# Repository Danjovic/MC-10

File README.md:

# MC-10
Tandy MC-10 computer related stuff

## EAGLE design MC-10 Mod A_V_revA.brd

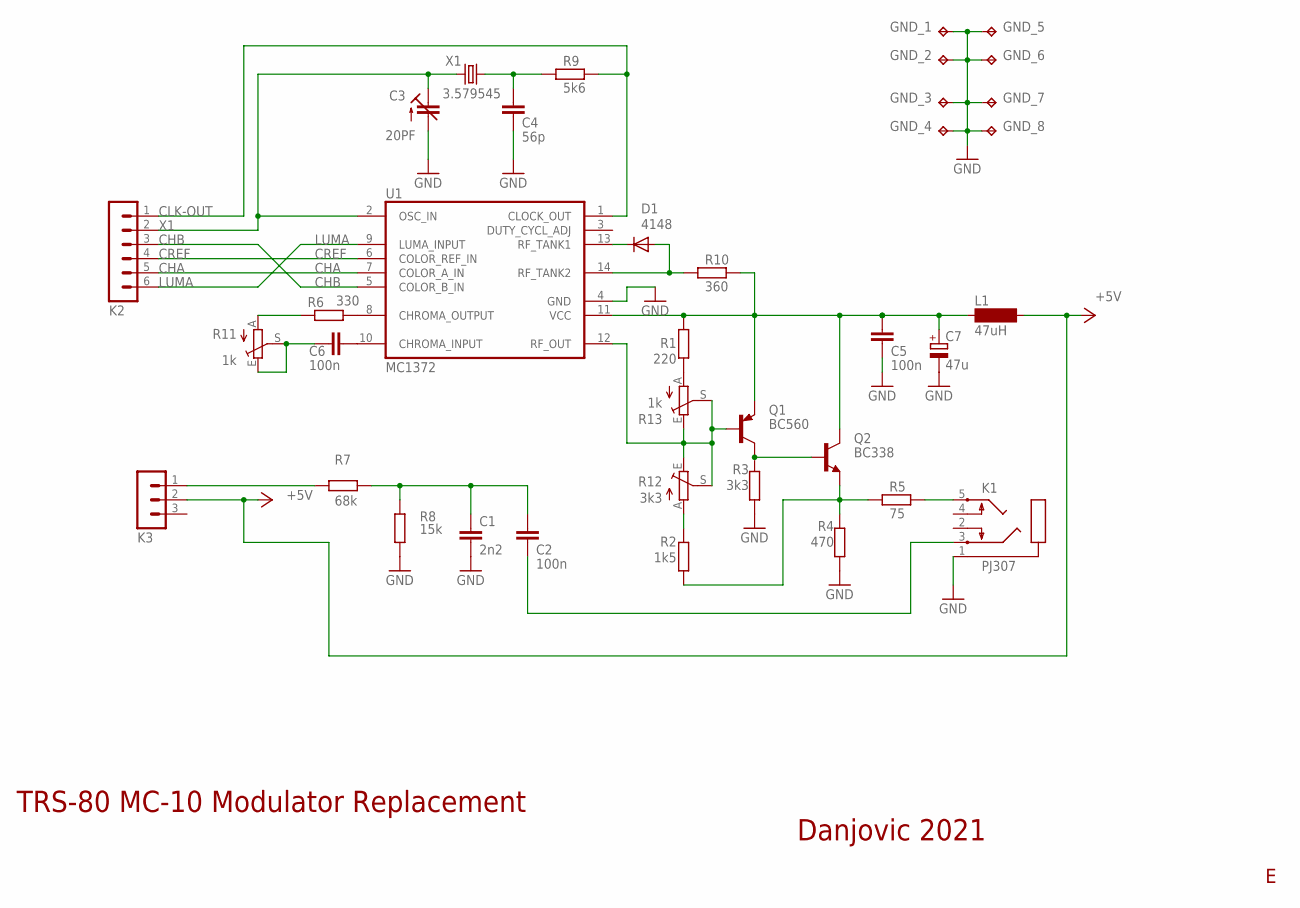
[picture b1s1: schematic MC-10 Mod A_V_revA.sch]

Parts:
C1: 2n2; C050-024X044
C2, C5, C6: 100n; C050-024X044
C3: 20PF; CTRIM3050.504
C4: 56p; C025-024X044
C7: 47u; E2,5-5
D1: 4148; D-5
GND_1, GND_2, GND_3, GND_4, GND_5, GND_6, GND_7, GND_8: TPPAD1-13; P1-13
K1: PJ307
K2: MA06-1
K3: MA03-1
L1: 47uH; BS75
Q1: BC560; TO92-EBC
Q2: BC338; TO92-EBC
R1: 220; 0204/7
R2: 1k5; 0204/7
R3: 3k3; 0204/7
R4: 470; 0204/7
R5: 75; 0204/7
R6: 330; 0204/7
R7: 68k; 0204/7
R8: 15k; 0204/7
R9: 5k6; 0204/7
R10: 360; 0204/7
R11, R13: 1k; RS3
R12: 3k3; RS3
U1: MC1372; DIL14
X1: 3.579545; HC49U70

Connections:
+5V: K3.2, L1.2
AUD-OUT: C2.2, K1.3
CHA: K2.5, U1.7 (COLOR_A_IN)
CHB: K2.3, U1.5 (COLOR_B_IN)
CLK-OUT: K2.1, R9.2, U1.1 (CLOCK_OUT)
CREF: K2.4, U1.6 (COLOR_REF_IN)
GND: C1.2, C3.2 (A), C4.2, C5.2, C7.-, GND_1.TP, GND_2.TP, GND_3.TP, GND_4.TP, GND_5.TP, GND_6.TP, GND_7.TP, GND_8.TP, K1.1, R3.1, R4.1, R8.1, U1.4 (GND)
LUMA: K2.6, U1.9 (LUMA_INPUT)
unnamed: R6.2, U1.8 (CHROMA_OUTPUT)
unnamed: C1.1, C2.1, R7.1, R8.2
unnamed: D1.C, U1.13 (RF_TANK1)
unnamed: R6.1, R11.A
unnamed: Q1.B, R12.E, R12.S, R13.E, R13.S, U1.12 (RF_OUT)
unnamed: C6.2, U1.10 (CHROMA_INPUT)
unnamed: C4.1, R9.1, X1.2
unnamed: R1.1, R13.A
unnamed: C6.1, R11.E, R11.S
unnamed: Q1.C, Q2.B, R3.2
unnamed: Q2.E, R2.1, R4.2, R5.1
unnamed: R2.2, R12.A
unnamed: D1.A, R10.1, U1.14 (RF_TANK2)
SOUND: K3.1, R7.2
VCC: C5.1, C7.+, L1.1, Q1.E, Q2.C, R1.2, R10.2, U1.11 (VCC)
VID-OUT: K1.5, R5.2
X1: C3.1 (E), K2.2, U1.2 (OSC_IN), X1.1

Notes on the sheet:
Danjovic 2021
TRS-80 MC-10 Modulator Replacement

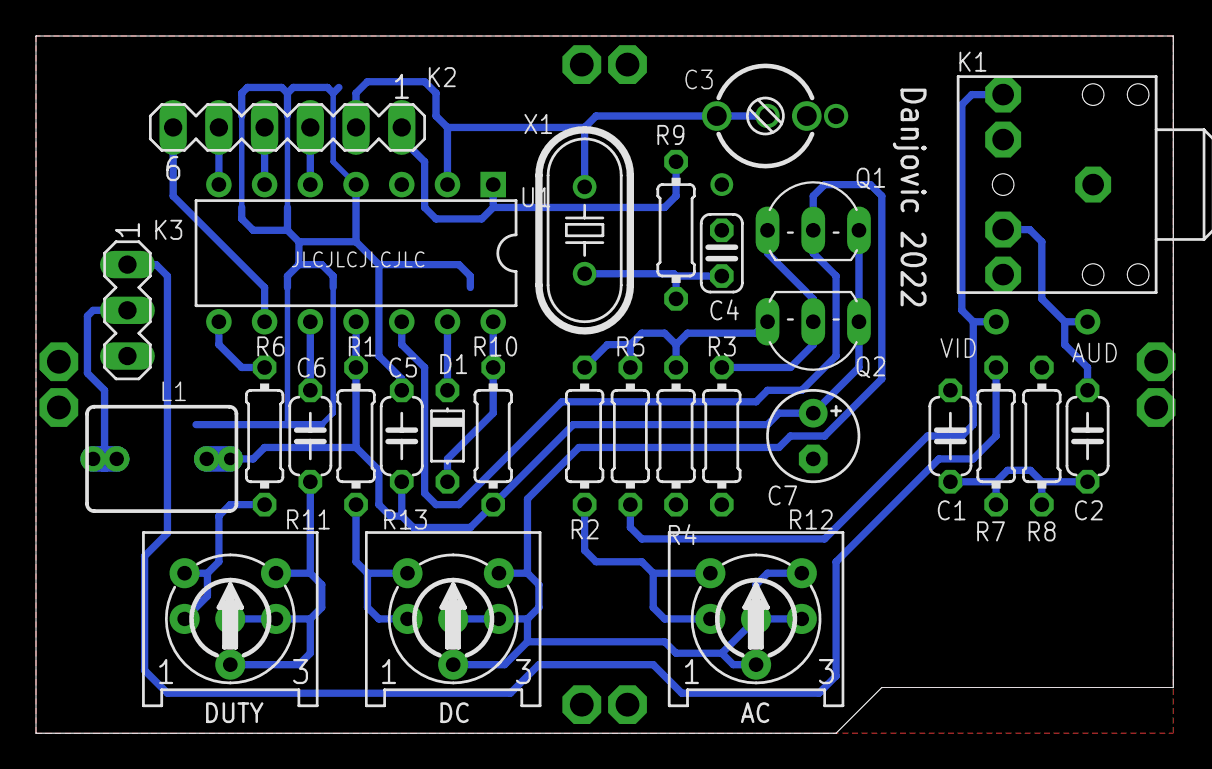
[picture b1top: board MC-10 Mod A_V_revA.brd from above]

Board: 2 copper layers, 63.2 x 38.7 mm, 37 parts (0 on the bottom side), 25 nets.

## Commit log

2021-09-24 Eagle Library for some MC-10 Chips
2021-09-24 Create LICENSE
2021-09-27 Added Edge Connector
2021-09-28 Added MC-10 schematics redrawn.
2021-09-28 added Eagle schematics
2021-09-29 RevA of schematics, corrected edge connector on library
    Rev A: /OE from SRAMs connected to GND, Selection signal names according to MC-10 service manual, Corrected opamp rails to +/-10V, deleted unused gates.
    Added blank positions on the edge connectors (equivalent to pins 35, 36)
2021-09-29 Corrected connection of 3.579545 MHz CLK and /WIN signal
2021-09-29 Further Correction on of 3.579545 MHz CLK and /WIN signal
2021-10-04 Schematics update, Added AV Mod schematics
    Schematics Rev C: Updated DIN connectors, added pinout on RF modulator, added Test Points
    Added Schematics for Audio-Video Mod (RF modulator replacement)
2021-10-30 Updated PCB for AV Mod
2021-10-30 Schematic imported in Kicad 5.1.2
2021-10-30 Added pdf for schematics imported in Kicad 5.1.2
2021-11-22 Updated AV mod Schematics and PCB
2023-08-16 schematics and library update
